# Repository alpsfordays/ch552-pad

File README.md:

# ch552-pad
A 3×5 CH552-based split keyboard.

The BOM is very simple; 6 SOT123 diode (SC88) packages, two 0.1µF capacitors, two 5.1K CC resistors and a USB-C connector per side. And, of course, 36 Cherry ML switches.

Licenced under the no wasteman's licence; for all intents and purposes, CC 4.0 BY-NC-SA, unless you're a wasteman, in which case you shouldn't be reading this.

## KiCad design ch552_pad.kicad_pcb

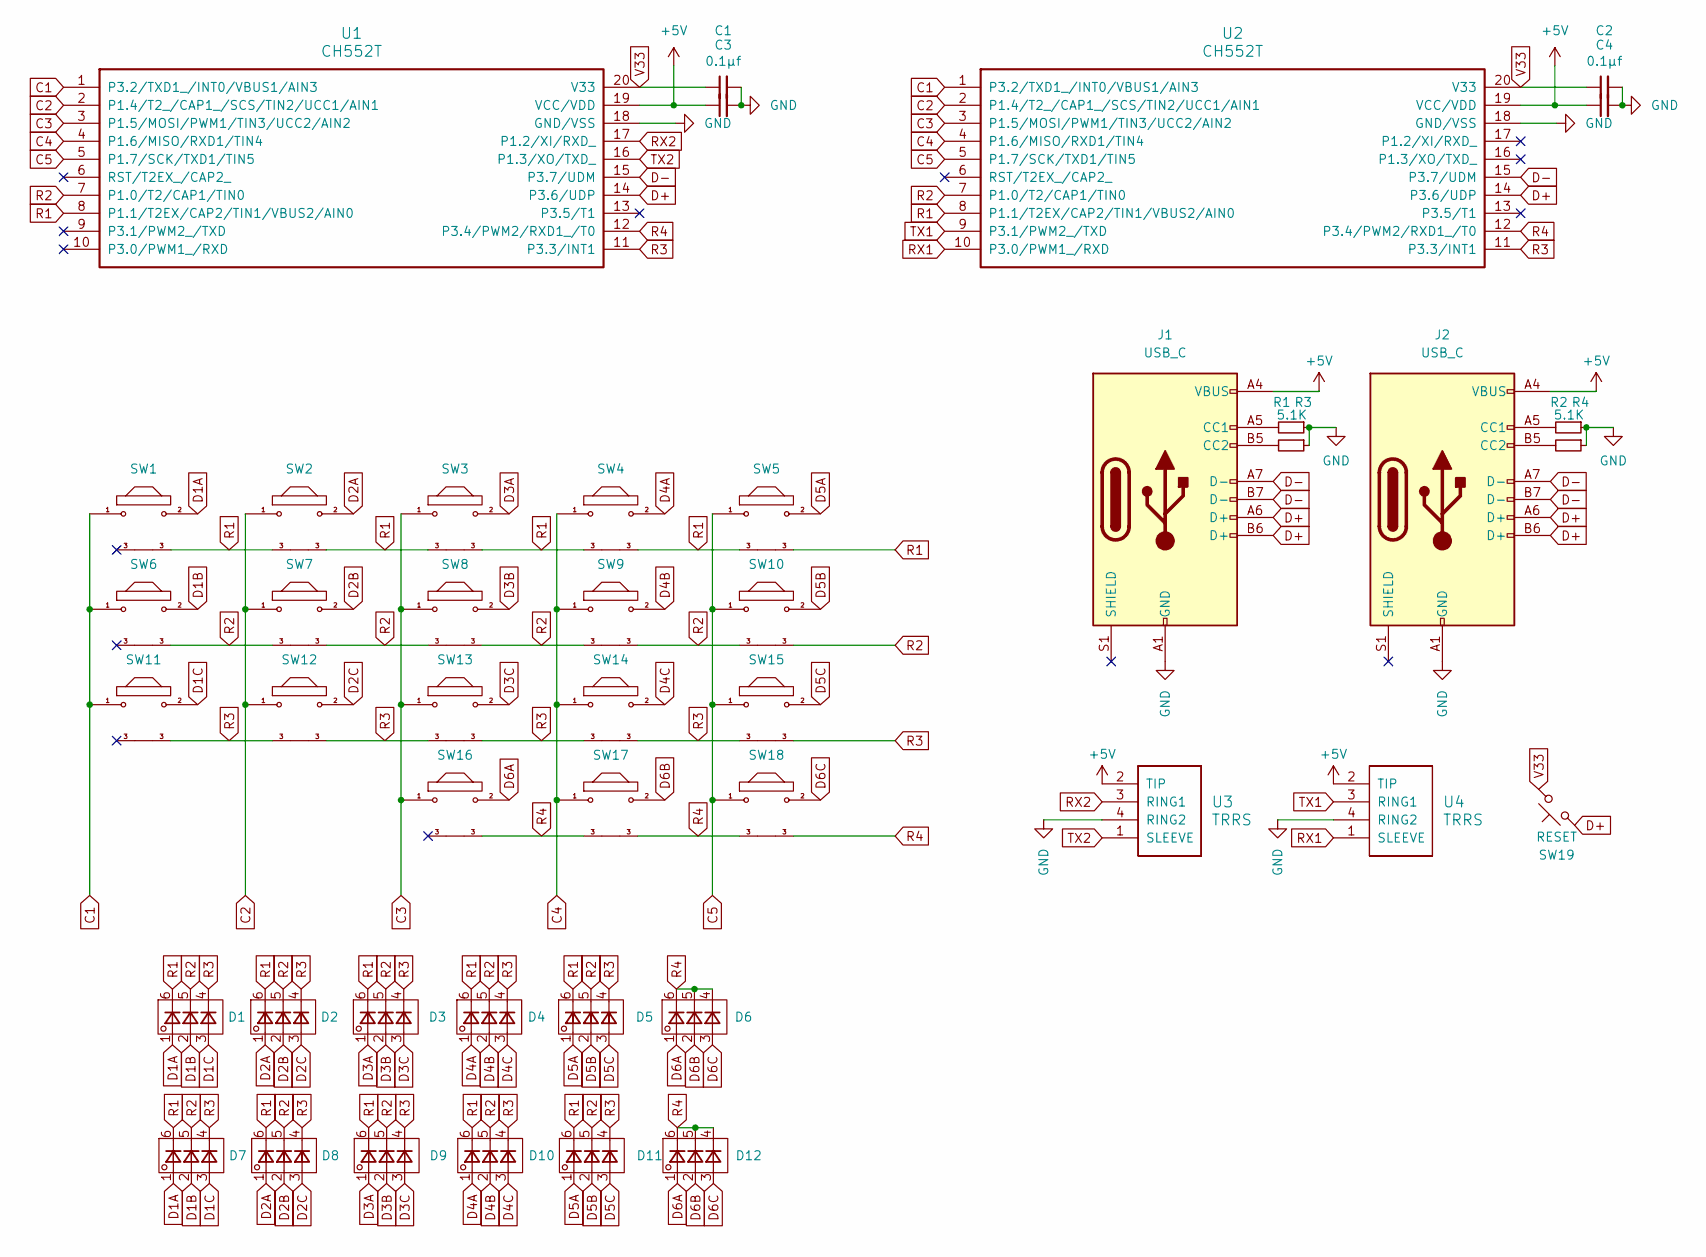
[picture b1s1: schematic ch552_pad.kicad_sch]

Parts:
C1, C2, C3, C4: 0.1µf; C_0603
D1, D2, D3, D4, D5, D6, D7, D8, D9, D10, D11, D12: SOT-363_SC-70-6
J1, J2: USB_C; TYPE-C-31-M-12
R1, R2, R3, R4: 5.1K; R_0603
SW1, SW2, SW3, SW4, SW5, SW6, SW7, SW8, SW9, SW10, SW11, SW12, SW13, SW14, SW15, SW16, SW17, SW18: ML; BothMasks_NoSilk_SW_Cherry_ML_1u_Centred
SW19: RESET; SW_Tactile_SPST_Angled_MJTP1117
U1, U2: CH552T; TSSOP-20_4.4x6.5mm_P0.65mm
U3, U4: TRRS; TRRS-PJ-320A-no-Fmask

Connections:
+5V: C3.1, C4.1, J1.A4 (VBUS), J1.A9 (VBUS), J1.B4 (VBUS), J1.B9 (VBUS), J2.A4 (VBUS), J2.A9 (VBUS), J2.B4 (VBUS), J2.B9 (VBUS), U1.19 (VCC/VDD), U2.19 (VCC/VDD), U3.2 (TIP), U4.2 (TIP)
C1: SW1.1, SW6.1, SW11.1, U1.1 (P3.2/TXD1_/INT0/VBUS1/AIN3), U2.1 (P3.2/TXD1_/INT0/VBUS1/AIN3)
C2: SW2.1, SW7.1, SW12.1, U1.2 (P1.4/T2_/CAP1_/SCS/TIN2/UCC1/AIN1), U2.2 (P1.4/T2_/CAP1_/SCS/TIN2/UCC1/AIN1)
C3: SW3.1, SW8.1, SW13.1, SW16.1, U1.3 (P1.5/MOSI/PWM1/TIN3/UCC2/AIN2), U2.3 (P1.5/MOSI/PWM1/TIN3/UCC2/AIN2)
C4: SW4.1, SW9.1, SW14.1, SW17.1, U1.4 (P1.6/MISO/RXD1/TIN4), U2.4 (P1.6/MISO/RXD1/TIN4)
C5: SW5.1, SW10.1, SW15.1, SW18.1, U1.5 (P1.7/SCK/TXD1/TIN5), U2.5 (P1.7/SCK/TXD1/TIN5)
D1A: D1.1, D7.1, SW1.2
D1B: D1.2, D7.2, SW6.2
D1C: D1.3, D7.3, SW11.2
D2A: D2.1, D8.1, SW2.2
D2B: D2.2, D8.2, SW7.2
D2C: D2.3, D8.3, SW12.2
D3A: D3.1, D9.1, SW3.2
D3B: D3.2, D9.2, SW8.2
D3C: D3.3, D9.3, SW13.2
D4A: D4.1, D10.1, SW4.2
D4B: D4.2, D10.2, SW9.2
D4C: D4.3, D10.3, SW14.2
D5A: D5.1, D11.1, SW5.2
D5B: D5.2, D11.2, SW10.2
D5C: D5.3, D11.3, SW15.2
D6A: D6.1, D12.1, SW16.2
D6B: D6.2, D12.2, SW17.2
D6C: D6.3, D12.3, SW18.2
D+: J1.A6 (D+), J1.B6 (D+), J2.A6 (D+), J2.B6 (D+), SW19.1, U1.14 (P3.6/UDP), U2.14 (P3.6/UDP)
D-: J1.A7 (D-), J1.B7 (D-), J2.A7 (D-), J2.B7 (D-), U1.15 (P3.7/UDM), U2.15 (P3.7/UDM)
GND: C1.2, C2.2, C3.2, C4.2, J1.A1 (GND), J1.A12 (GND), J1.B1 (GND), J1.B12 (GND), J2.A1 (GND), J2.A12 (GND), J2.B1 (GND), J2.B12 (GND), R1.1, R2.1, R3.1, R4.1, U1.18 (GND/VSS), U2.18 (GND/VSS), U3.4 (RING2), U4.4 (RING2)
unnamed: J1.A5 (CC1), R1.2
unnamed: J1.B5 (CC2), R3.2
unnamed: J2.A5 (CC1), R2.2
unnamed: J2.B5 (CC2), R4.2
R1: D1.6, D2.6, D3.6, D4.6, D5.6, D7.6, D8.6, D9.6, D10.6, D11.6, SW1.3, SW2.3, SW3.3, SW4.3, SW5.3, U1.8 (P1.1/T2EX/CAP2/TIN1/VBUS2/AIN0), U2.8 (P1.1/T2EX/CAP2/TIN1/VBUS2/AIN0)
R2: D1.5, D2.5, D3.5, D4.5, D5.5, D7.5, D8.5, D9.5, D10.5, D11.5, SW6.3, SW7.3, SW8.3, SW9.3, SW10.3, U1.7 (P1.0/T2/CAP1/TIN0), U2.7 (P1.0/T2/CAP1/TIN0)
R3: D1.4, D2.4, D3.4, D4.4, D5.4, D7.4, D8.4, D9.4, D10.4, D11.4, SW11.3, SW12.3, SW13.3, SW14.3, SW15.3, U1.11 (P3.3/INT1), U2.11 (P3.3/INT1)
R4: D6.4, D6.5, D6.6, D12.4, D12.5, D12.6, SW16.3, SW17.3, SW18.3, U1.12 (P3.4/PWM2/RXD1_/T0), U2.12 (P3.4/PWM2/RXD1_/T0)
RX1: U2.10 (P3.0/PWM1_/RXD), U4.1 (SLEEVE)
RX2: U1.17 (P1.2/XI/RXD_), U3.3 (RING1)
TX1: U2.9 (P3.1/PWM2_/TXD), U4.3 (RING1)
TX2: U1.16 (P1.3/XO/TXD_), U3.1 (SLEEVE)
V33: C1.1, C2.1, SW19.2, U1.20 (V33), U2.20 (V33)

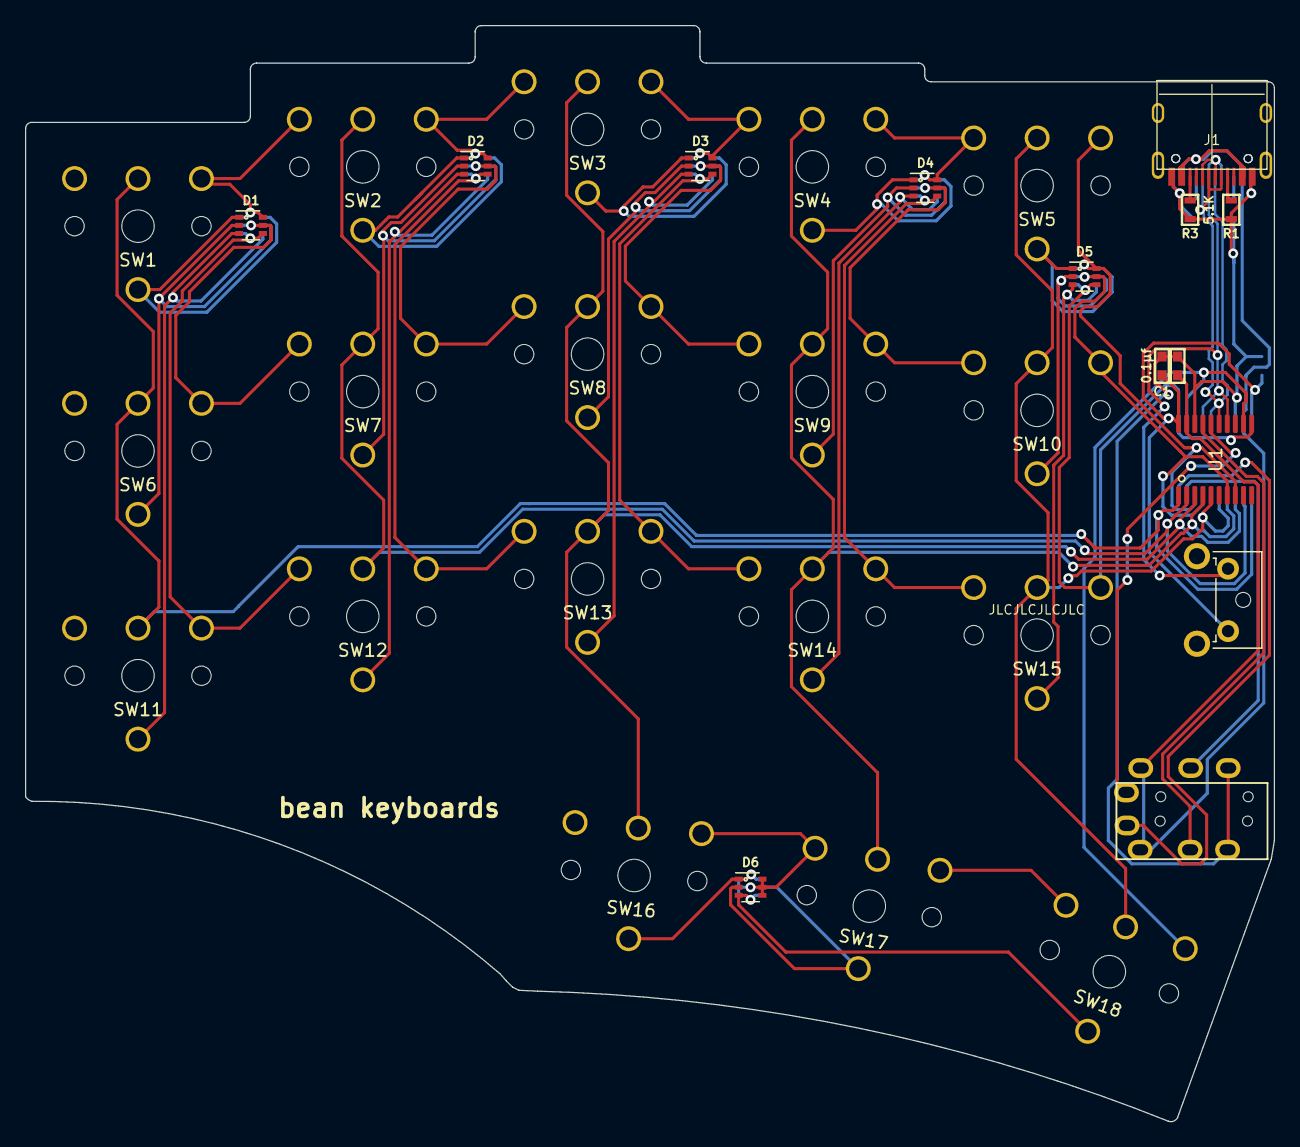
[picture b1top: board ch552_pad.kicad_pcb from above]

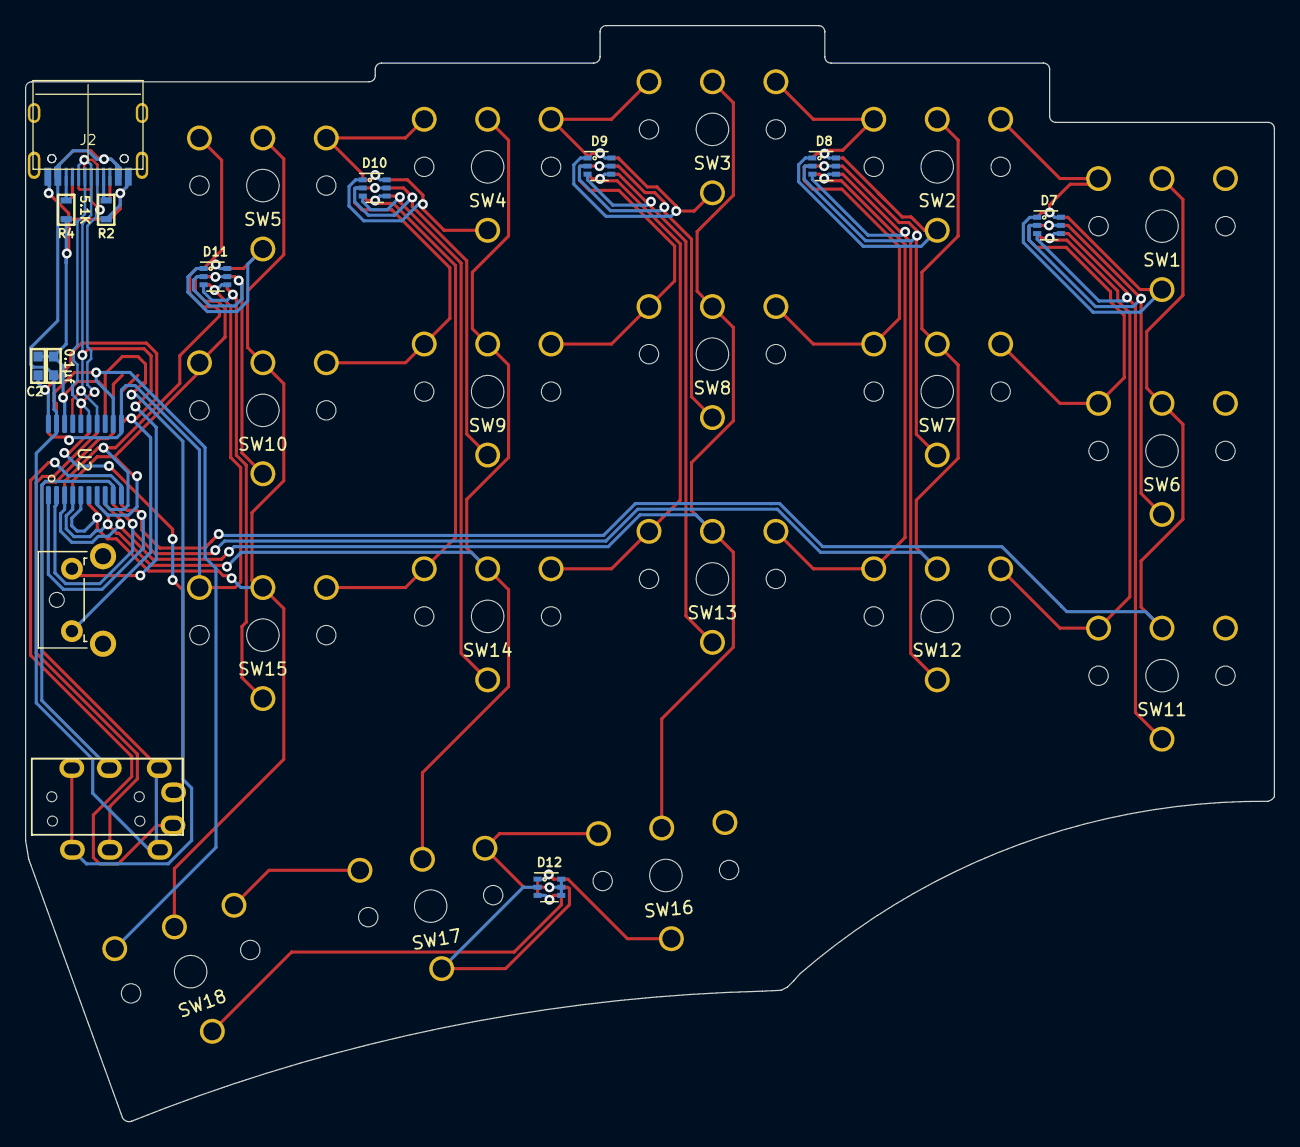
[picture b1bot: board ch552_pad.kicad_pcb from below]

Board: 2 copper layers, 100.0 x 87.8 mm, 45 parts (13 on the bottom side), 40 nets.

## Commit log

2024-10-22 Add files
